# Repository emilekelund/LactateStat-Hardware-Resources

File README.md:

# LactateStat-Hardware-Resources

This is the hardware resources used in my master thesis: LactateStat: Wearable Electronics and Software for Real-Time Lactate Monitoring in Sweat

The PCB was created using KiCad version 5.1.6 and they were manufactured and assembled by PCBWay.

## Copyright disclaimer

Copyright (c) 2021 Emil Ekelund

Permission is hereby granted, free of charge, to any person obtaining a copy of this software and associated documentation files (the "Software"), to deal in the Software without restriction, including without limitation the rights to use, copy, modify, merge, publish, distribute, sublicense, and/or sell copies of the Software, and to permit persons to whom the Software is furnished to do so, subject to the following conditions:

The above copyright notice and this permission notice shall be included in all copies or substantial portions of the Software.

THE SOFTWARE IS PROVIDED "AS IS", WITHOUT WARRANTY OF ANY KIND, EXPRESS OR IMPLIED, INCLUDING BUT NOT LIMITED TO THE WARRANTIES OF MERCHANTABILITY, FITNESS FOR A PARTICULAR PURPOSE AND NONINFRINGEMENT. IN NO EVENT SHALL THE AUTHORS OR COPYRIGHT HOLDERS BE LIABLE FOR ANY CLAIM, DAMAGES OR OTHER LIABILITY, WHETHER IN AN ACTION OF CONTRACT, TORT OR OTHERWISE, ARISING FROM, OUT OF OR IN CONNECTION WITH THE SOFTWARE OR THE USE OR OTHER DEALINGS IN THE SOFTWARE.

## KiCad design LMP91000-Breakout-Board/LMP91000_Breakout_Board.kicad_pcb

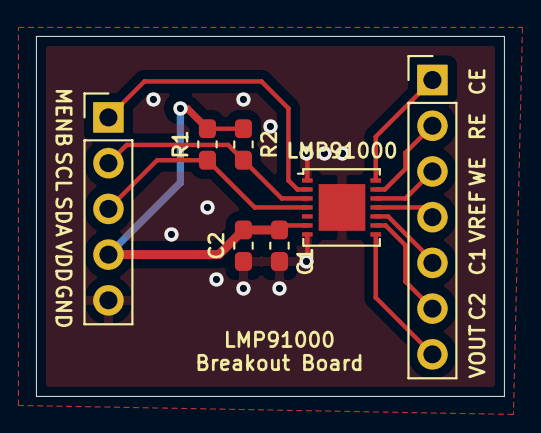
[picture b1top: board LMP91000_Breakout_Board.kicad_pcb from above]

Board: 2 copper layers, 26.0 x 20.0 mm, 7 parts (0 on the bottom side), 12 nets.

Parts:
C1: 0.1u; C_0603_1608Metric_Pad1.05x0.95mm_HandSolder
C2: 1u; C_0603_1608Metric_Pad1.05x0.95mm_HandSolder
J1: Conn_01x07; PinHeader_1x07_P2.54mm_Vertical
J2: Conn_01x05; PinHeader_1x05_P2.54mm_Vertical
LMP91000: LMP91000SD_NOPB; WSON-14-1EP_4.0x4.0mm_P0.5mm_EP2.6x2.6mm
R1, R2: 10K; R_0603_1608Metric_Pad1.05x0.95mm_HandSolder

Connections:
C1: J1.5, LMP91000.10
C2: J1.6, LMP91000.9
CE: J1.1, LMP91000.14
GND: C1.2, C2.2, J2.5, LMP91000.1, LMP91000.7, LMP91000.15
MENB: J2.1, LMP91000.2
RE: J1.2, LMP91000.13
SCL: J2.2, LMP91000.3, R2.2
SDA: J2.3, LMP91000.4, R1.2
VDD: C1.1, C2.1, J2.4, LMP91000.6, R1.1, R2.1
VOUT: J1.7, LMP91000.8
VREF: J1.4, LMP91000.11
WE: J1.3, LMP91000.12

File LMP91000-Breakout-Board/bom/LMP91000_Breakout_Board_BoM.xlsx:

Id | Designator | Package | Quantity | Designation | Supplier and ref | Unit Price ($)
1 | LMP91000 | WSON-14-1EP_4.0x4.0mm_P0.5mm_EP2.6x2.6mm | 1 | LMP91000SD_NOPB | Texas Instruments LMP91000SD/NOPB | 5
2 | R2,R1 | R_0603_1608Metric_Pad1.05x0.95mm_HandSolder | 2 | 10K | Stackpole Electronics Inc RNCP0603FTD10K0 | 0.1
3 | C2 | C_0603_1608Metric_Pad1.05x0.95mm_HandSolder | 1 | 1u | Samsung Electro-Mechanics CL10B104KB8NNNL | 0.1
4 | C1 | C_0603_1608Metric_Pad1.05x0.95mm_HandSolder | 1 | 0.1u | Samsung Electro-Mechanics CL10B105KP8NNNC | 0.1

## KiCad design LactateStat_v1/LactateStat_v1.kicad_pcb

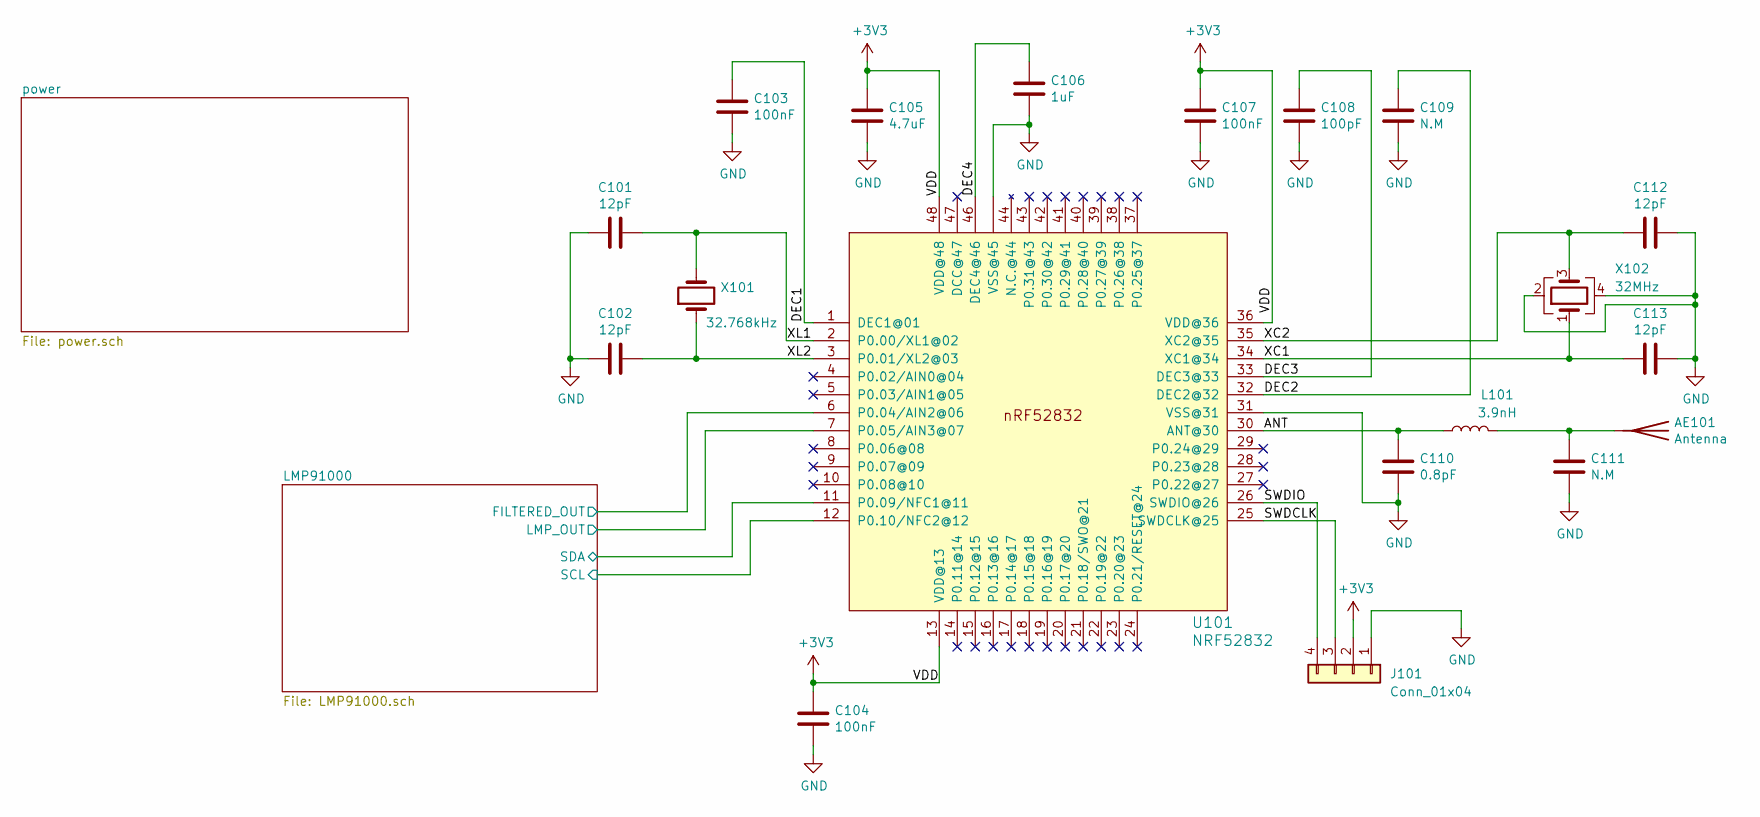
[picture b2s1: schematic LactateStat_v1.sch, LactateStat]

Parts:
AE101: Antenna
C101, C102, C112, C113: 12pF; C_0402_1005Metric
C103, C104, C107: 100nF; C_0402_1005Metric
C105: 4.7uF; C_0603_1608Metric
C106: 1uF; C_0603_1608Metric
C108: 100pF; C_0402_1005Metric
C109: N.M; C_0402_1005Metric
C110: 0.8pF; C_0402_1005Metric
C111: N.M; C_0603_1608Metric
J101: Conn_01x04; PinHeader_1x04_P2.54mm_Vertical
L101: 3.9nH; L_0402_1005Metric
U101: NRF52832; nRF52832_with_via_pads
X101: 32.768kHz; Crystal_SMD_3215-2Pin_3.2x1.5mm
X102: 32MHz; Crystal_SMD_2016-4Pin_2.0x1.6mm

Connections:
+3V3: C104.1, C105.1, C107.1, J101.2, U101.13 (VDD@13), U101.36 (VDD@36), U101.48 (VDD@48); also elsewhere on the board
/ANT: C110.1, L101.1, U101.30 (ANT@30)
/DEC1: C103.1, U101.1 (DEC1@01)
/DEC2: C109.1, U101.32 (DEC2@32)
/DEC3: C108.1, U101.33 (DEC3@33)
/DEC4: C106.1, U101.46 (DEC4@46)
/LMP91000/FILTERED_OUT: U101.6 (P0.04/AIN2@06); also elsewhere on the board
/LMP91000/LMP_OUT: U101.7 (P0.05/AIN3@07); also elsewhere on the board
/LMP91000/SCL: U101.12 (P0.10/NFC2@12); also elsewhere on the board
/LMP91000/SDA: U101.11 (P0.09/NFC1@11); also elsewhere on the board
/SWDCLK: J101.3, U101.25 (SWDCLK@25)
/SWDIO: J101.4, U101.26 (SWDIO@26)
/XC1: C113.2, U101.34 (XC1@34), X102.1
/XC2: C112.2, U101.35 (XC2@35), X102.3
/XL1: C101.1, U101.2 (P0.00/XL1@02), X101.2
/XL2: C102.1, U101.3 (P0.01/XL2@03), X101.1
GND: C101.2, C102.2, C103.2, C104.2, C105.2, C106.2, C107.2, C108.2, C109.2, C110.2, C111.2, C112.1, C113.1, J101.1, U101.31 (VSS@31), U101.45 (VSS@45), U101.PAD (VSS@45), U101.PAD@VIA01 (VSS@45), U101.PAD@VIA02 (VSS@45), U101.PAD@VIA03 (VSS@45), U101.PAD@VIA04 (VSS@45), U101.PAD@VIA05 (VSS@45), U101.PAD@VIA06 (VSS@45), U101.PAD@VIA07 (VSS@45), U101.PAD@VIA08 (VSS@45), U101.PAD@VIA09 (VSS@45), U101.PAD@VIA10 (VSS@45), U101.PAD@VIA11 (VSS@45), U101.PAD@VIA12 (VSS@45), U101.PAD@VIA13 (VSS@45), U101.PAD@VIA14 (VSS@45), U101.PAD@VIA15 (VSS@45), U101.PAD@VIA16 (VSS@45), X102.2, X102.4; also elsewhere on the board
unnamed: AE101.1, C111.1, L101.2

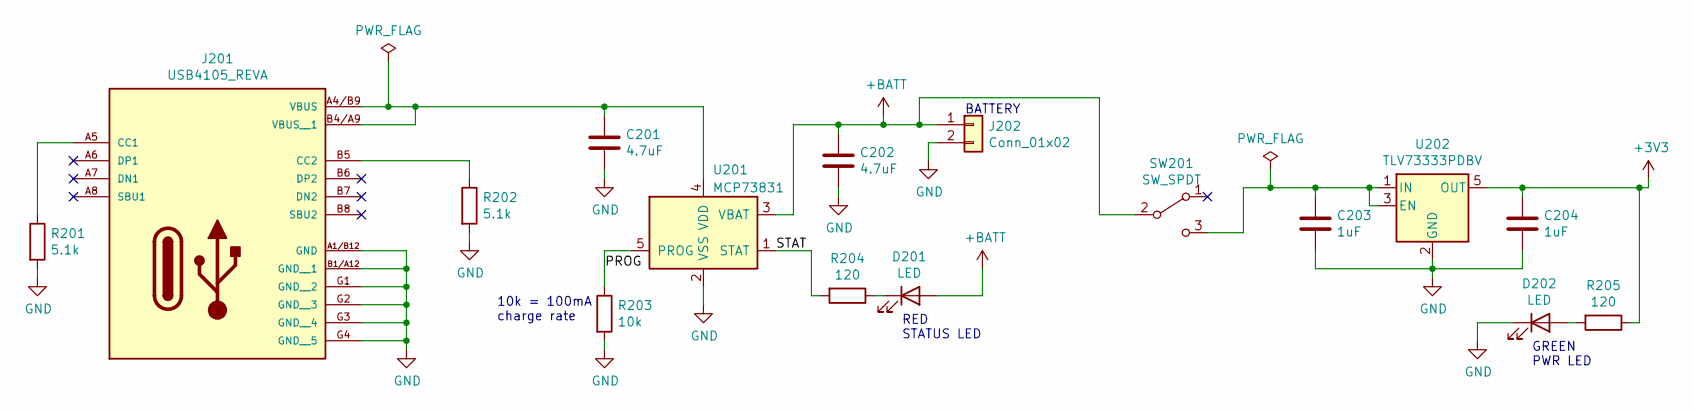
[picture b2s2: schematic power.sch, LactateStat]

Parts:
C201, C202: 4.7uF; C_0402_1005Metric
C203, C204: 1uF; C_0402_1005Metric
D201, D202: LED; D_0402_1005Metric
J201: USB4105_REVA; GCT_USB4105_REVA
J202: Conn_01x02; PinHeader_1x02_P1.27mm_Vertical
R201, R202: 5.1k; R_0201_0603Metric
R203: 10k; R_0402_1005Metric
R204, R205: 120; R_0201_0603Metric
SW201: SW_SPDT; CL-SB-12B
U201: MCP73831; SOT-23-5
U202: TLV73333PDBV; SOT-23-5

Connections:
+3V3: C204.1, R205.1, U202.5 (OUT); also elsewhere on the board
+BATT: C202.1, D201.2 (A), J202.1, SW201.2 (B), U201.3 (VBAT)
/power/PROG: R203.1, U201.5 (PROG)
/power/STAT: R204.2, U201.1 (STAT)
GND: C201.2, C202.2, C203.2, C204.2, D202.1 (K), J201.A1/B12 (GND), J201.B1/A12 (GND__1), J201.G1 (GND__2), J201.G2 (GND__3), J201.G3 (GND__4), J201.G4 (GND__5), J202.2, R201.2, R202.2, R203.2, U201.2 (VSS), U202.2 (GND); also elsewhere on the board
unnamed: C201.1, J201.A4/B9 (VBUS), J201.B4/A9 (VBUS__1), U201.4 (VDD)
unnamed: C203.1, SW201.3 (C), U202.1 (IN), U202.3 (EN)
unnamed: D201.1 (K), R204.1
unnamed: D202.2 (A), R205.2
unnamed: J201.A5 (CC1), R201.1
unnamed: J201.B5 (CC2), R202.1

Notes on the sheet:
10k = 100mA charge rate
RED STATUS LED
GREEN PWR LED
BATTERY

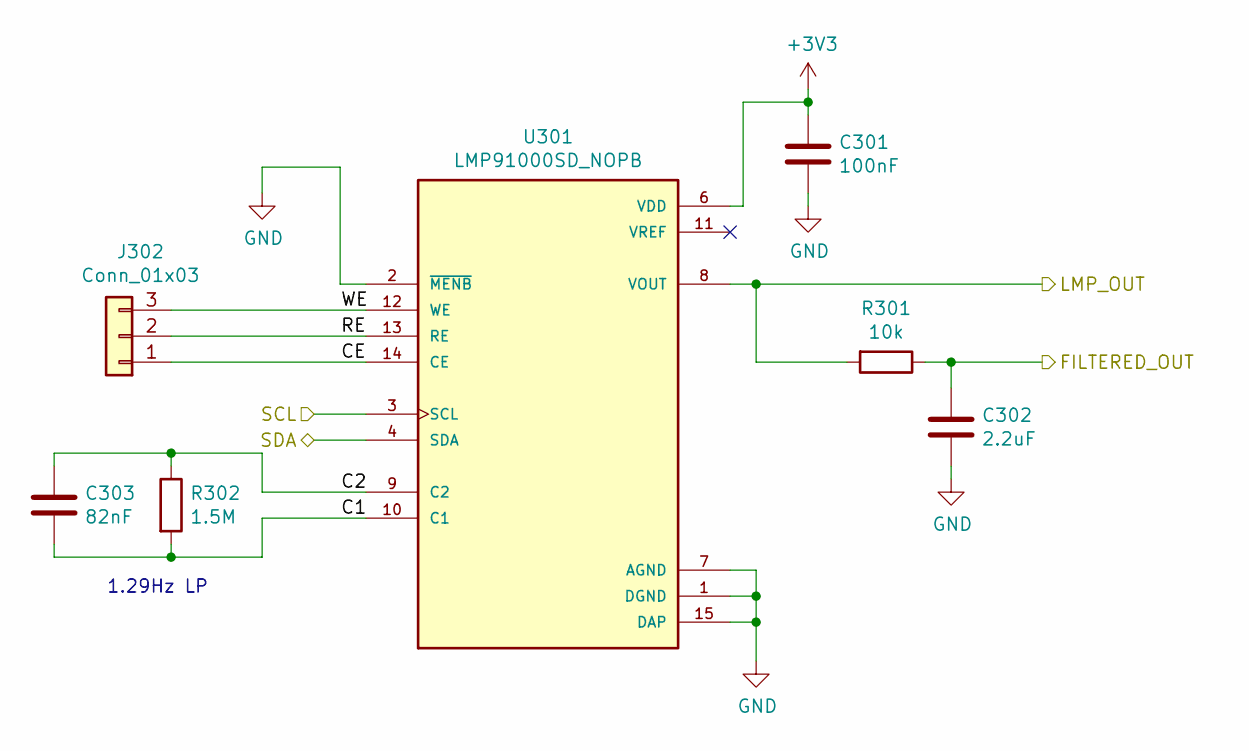
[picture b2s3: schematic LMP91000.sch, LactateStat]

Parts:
C301: 100nF; C_0402_1005Metric
C302: 2.2uF; C_0201_0603Metric
C303: 82nF; C_0402_1005Metric
J302: Conn_01x03; PinHeader_1x03_P2.54mm_Vertical
R301: 10k; R_0201_0603Metric
R302: 1.5M; R_0402_1005Metric
U301: LMP91000SD_NOPB; WSON-14-1EP_4.0x4.0mm_P0.5mm_EP2.6x2.6mm; PARTREV I

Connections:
+3V3: C301.1, U301.6 (VDD); also elsewhere on the board
/LMP91000/C1: C303.2, R302.2, U301.10 (C1)
/LMP91000/C2: C303.1, R302.1, U301.9 (C2)
/LMP91000/CE: J302.1, U301.14 (CE)
/LMP91000/FILTERED_OUT: C302.1, R301.1; also elsewhere on the board
/LMP91000/LMP_OUT: R301.2, U301.8 (VOUT); also elsewhere on the board
/LMP91000/RE: J302.2, U301.13 (RE)
/LMP91000/SCL: U301.3 (SCL); also elsewhere on the board
/LMP91000/SDA: U301.4 (SDA); also elsewhere on the board
/LMP91000/WE: J302.3, U301.12 (WE)
GND: C301.2, C302.2, U301.1 (DGND), U301.2 (~MENB), U301.7 (AGND), U301.15 (DAP); also elsewhere on the board

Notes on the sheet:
1.29Hz LP

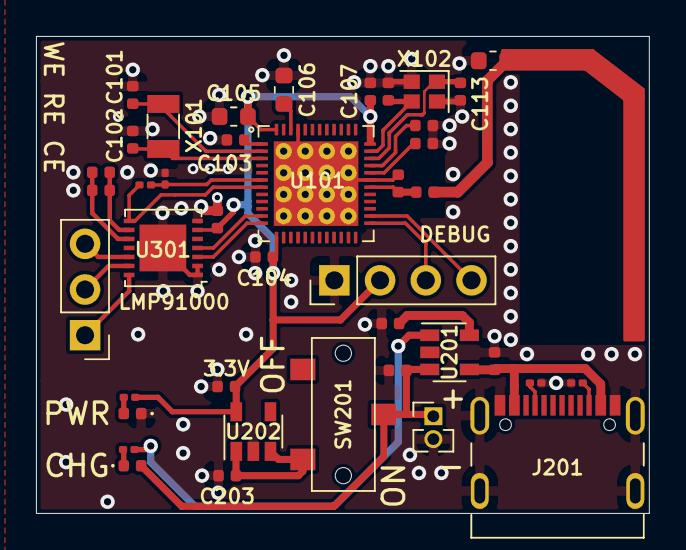
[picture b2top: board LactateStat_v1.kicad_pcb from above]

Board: 2 copper layers, 34.1 x 26.5 mm, 41 parts (0 on the bottom side), 32 nets.

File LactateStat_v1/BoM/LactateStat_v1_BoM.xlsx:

Item | Designator | Description / Value | Package | Manufacturer | Manufacturer part # | Quantity
1 | R205,R204 | 120 | R_0201_0603Metric |  |  | 2
2 | D201 | LED RED | D_0402_1005Metric |  |  | 1
3 | D202 | LED GREEN | D_0402_1005Metric |  |  | 1
4 | R202,R201 | 5.1k | R_0201_0603Metric |  |  | 2
5 | C101,C102,C112,C113 | 12pF NP0 2% | C_0402_1005Metric |  |  | 4
6 | C103,C104,C107,C301 | 100nF, X7R, 10% | C_0402_1005Metric |  |  | 4
7 | C105 | 4.7uF, X5R, 10% | C_0603_1608Metric |  |  | 1
8 | C106 | 1.0uF X7R 10% | C_0603_1608Metric |  |  | 1
9 | C108 | 100pF, NP0, 5% | C_0402_1005Metric |  |  | 1
10 | C110 | 0.8pF, NP0, 5% | C_0402_1005Metric |  |  | 1
11 | L101 | 3.9nH 5% | L_0402_1005Metric |  |  | 1
12 | U101 | NRF52832-QFAB-R | 48-VFQFN |  |  | 1
13 | X101 | 32.768kHz 9pF 20ppm | Crystal_SMD_3215-2Pin_3.2x1.5mm |  |  | 1
14 | X102 | 32MHz 8pF 10ppm | Crystal_SMD_2016-4Pin_2.0x1.6mm |  |  | 1
15 | C201,C202 | 4.7uF X7R | C_0402_1005Metric |  |  | 2
16 | C203,C204 | 1uF | C_0402_1005Metric |  |  | 2
17 | C302 | 2.2uF | C_0201_0603Metric |  |  | 1
18 | C303 | 82nF 10% | C_0402_1005Metric |  |  | 1
20 | J201 | USB C RECEPTACLE | GCT_USB4105_REVA | GCT | USB4110-GF-A | 1
23 | R203 | 10k | R_0402_1005Metric |  |  | 1
24 | R301 | 10k | R_0201_0603Metric |  |  | 1
25 | R302 | 1.5M 1% | R_0402_1005Metric |  |  | 1
26 | SW201 | SW_SPDT | CL-SB-12B | Nidec Copal Electronics | CL-SB-12B-01T | 1
27 | U201 | MCP73831 | SOT-23-5 |  |  | 1
28 | U202 | TLV73333PDBV | SOT-23-5 |  |  | 1
29 | U301 | LMP91000SD_NOPB | WSON-14-1EP_4.0x4.0mm_P0.5mm_EP2.6x2.6mm |  |  | 1

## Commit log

2021-05-10 Add design file for the case
